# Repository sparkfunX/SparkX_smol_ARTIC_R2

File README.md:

# SparkX smôl ARTIC R2

[*SparkX smôl ARTIC R2 (SPX-18618)*](https://www.sparkfun.com/products/18618)

The ARGOS ARTIC R2 satellite communication chipset in smôl format.

## Repository Contents

- [**/Hardware**](./Hardware) - Eagle PCB, SCH and LBR design files
- [**LICENSE.md**](./LICENSE.md) - contains the licence information

## Product Versions

- [SPX-18618](https://www.sparkfun.com/products/18618) - Original SparkX Release.

## Thanks

The ARTIC R2 circuit is a remix of the reference design kindly provided by the [Arribada Initiative](https://arribada.org/) and Icoteq Ltd.

## License Information

This product is _**open source**_!

Please review the LICENSE.md file for license information.

If you have any questions or concerns on licensing, please contact technical support on our [SparkFun forums](https://forum.sparkfun.com/viewforum.php?f=123).

Distributed as-is; no warranty is given.

- Your friends at SparkFun.

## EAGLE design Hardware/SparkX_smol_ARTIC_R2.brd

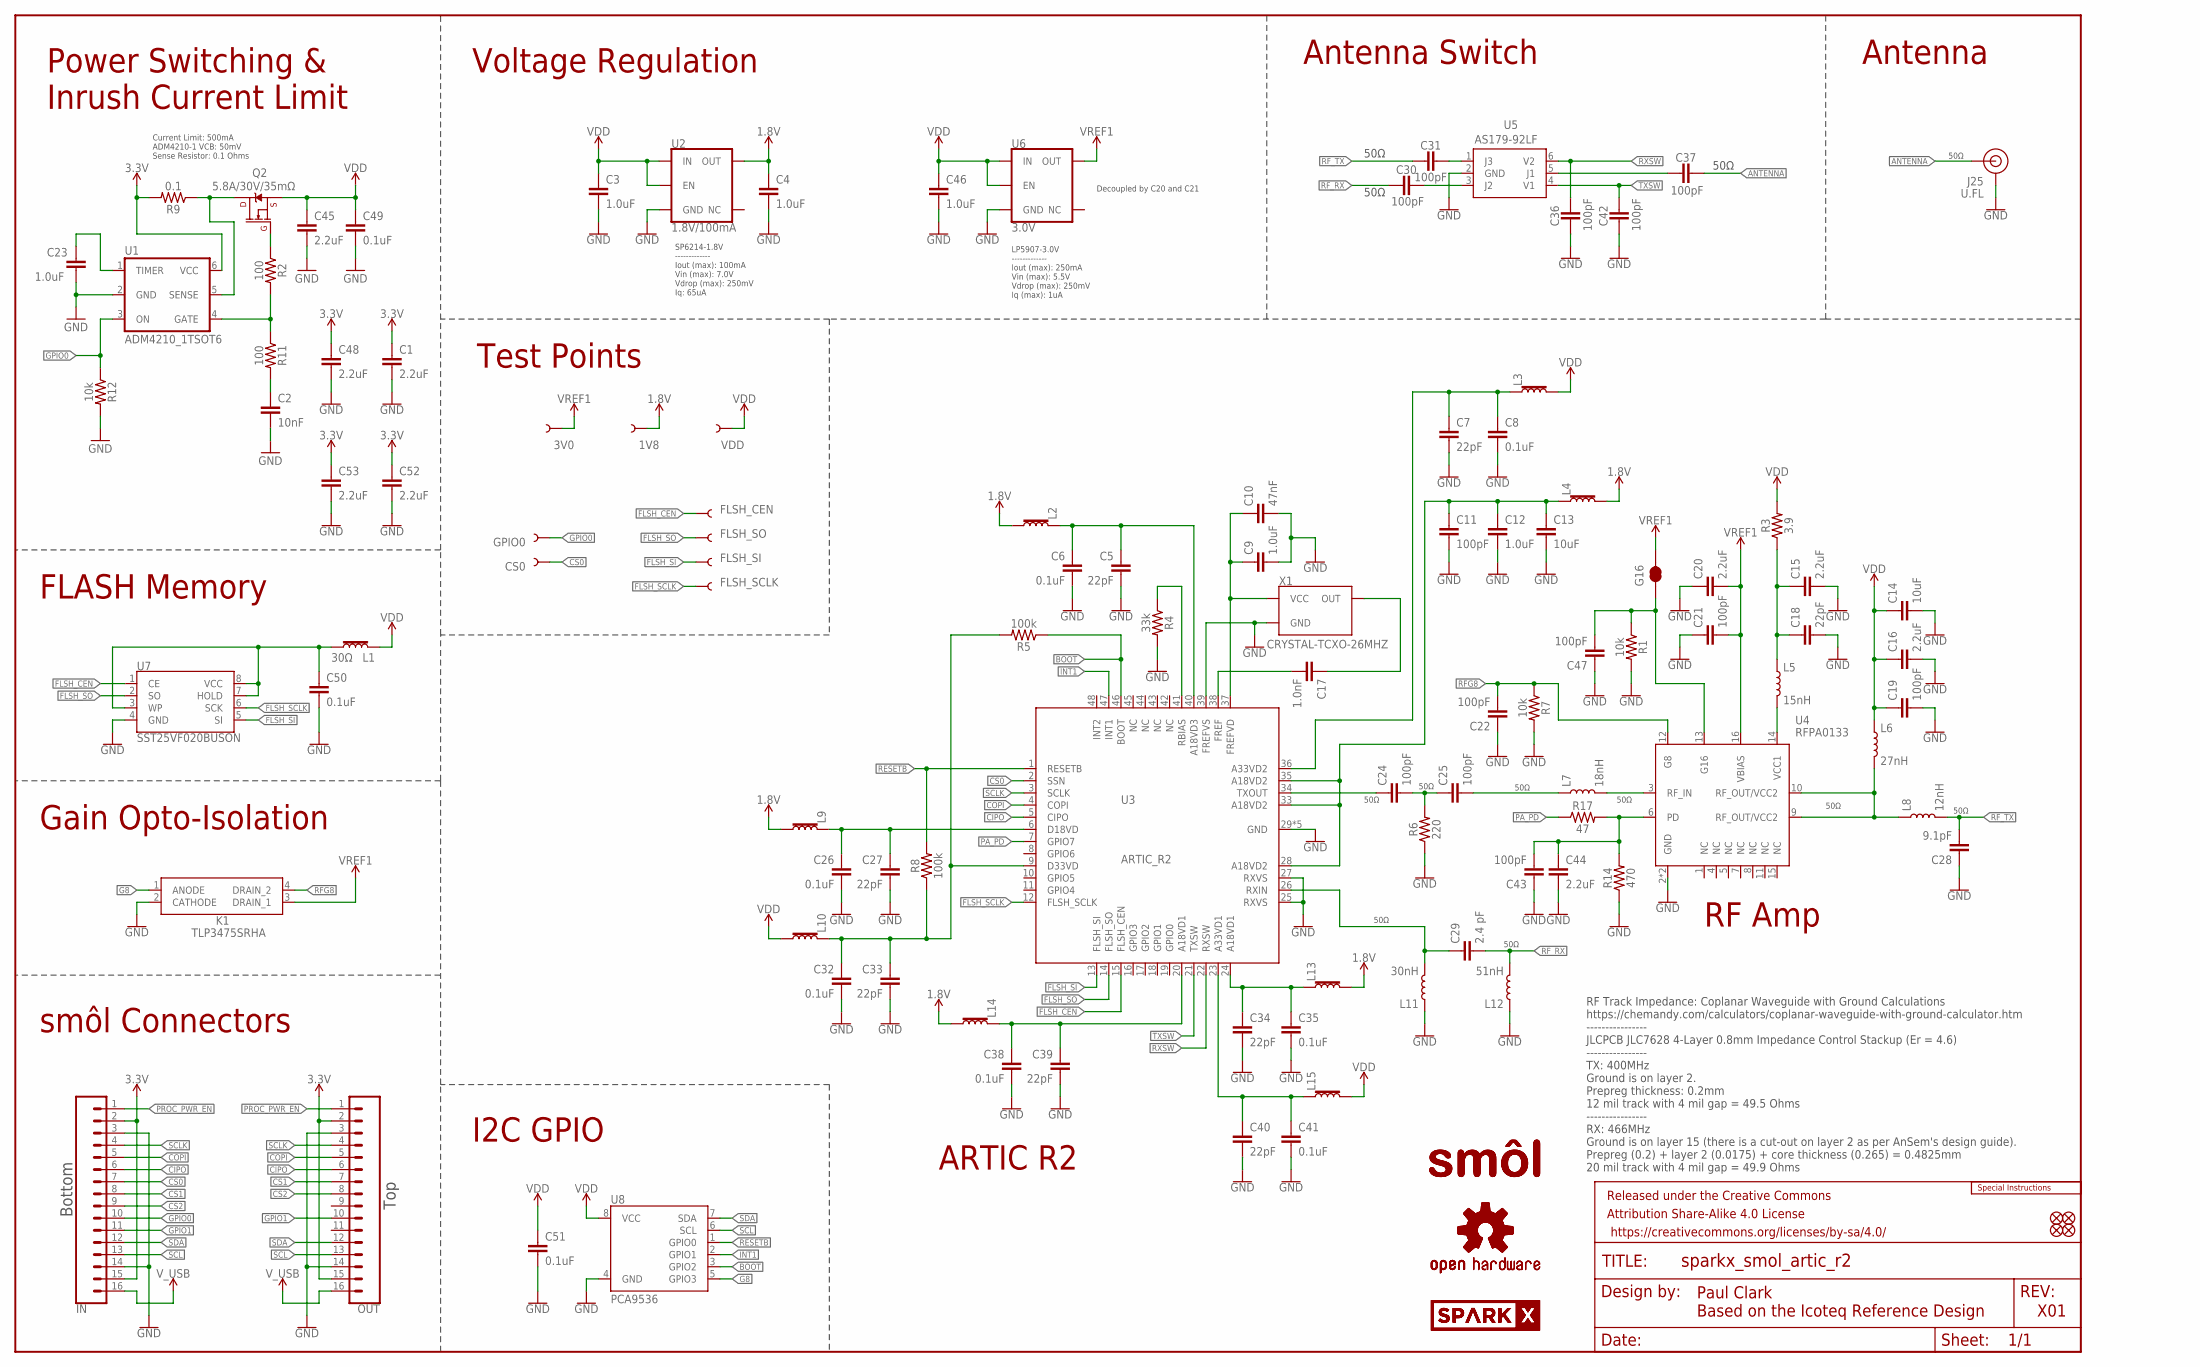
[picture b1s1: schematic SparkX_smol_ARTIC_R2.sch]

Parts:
1V8, 3V0: TEST-POINT3; PAD.03X.03
C1, C15, C16, C20, C44, C45, C48, C52, C53: 2.2uF; 0402-TIGHT
C2: 10nF; 0402-TIGHT
C3, C4, C9, C12, C23, C46: 1.0uF; 0402-TIGHT
C5, C7, C18, C27, C33, C34, C39, C40: 22pF; 0402-TIGHT
C6, C8, C26, C32, C35, C38, C41, C49, C50, C51: 0.1uF; 0402-TIGHT
C10: 47nF; 0402-TIGHT
C11, C19, C21, C22, C24, C25, C30, C31, C36, C37, C42, C43, C47: 100pF; 0402-TIGHT
C13, C14: 10uF; 0402-TIGHT
C17: 1.0nF; 0402-TIGHT
C28: 9.1pF; 0402-TIGHT
C29: 2.4 pF; 0402_MURATA
CS0: TEST-POINT3; PAD.03X.03
FD1, FD2, FD3, FD4: FIDUCIALUFIDUCIAL; FIDUCIAL-MICRO
FLSH_CEN: TEST-POINT3; PAD.03X.03
FLSH_SCLK: TEST-POINT3; PAD.03X.03
FLSH_SI: TEST-POINT3; PAD.03X.03
FLSH_SO: TEST-POINT3; PAD.03X.03
FRAME1: FRAME-LEDGER; CREATIVE_COMMONS
G16: JUMPER-SMT_2_NC_TRACE_NO-SILK; SMT-JUMPER_2_NC_TRACE_NO-SILK
GPIO0: TEST-POINT3; PAD.03X.03
IN: CONN_16FPC_16_0.5MM; FPC_16_0.5MM
J25: U.FL; U.FL_REDUCED_FOOTPRINT
K1: TLP3475SRHA
L1, L2, L3, L4, L9, L10, L13, L14, L15: 30Ω; 0402-TIGHT
L5: 15nH; 0402_COILCRAFT
L6: 27nH; 0402_COILCRAFT
L7: 18nH; 0402_COILCRAFT
L8: 12nH; 0402_COILCRAFT
L11: 30nH; 0402_COILCRAFT
L12: 51nH; 0402_COILCRAFT
LOGO1: SPECIAL_INSTRUCTIONS-ORDERING; ORDERING_INSTRUCTIONS
LOGO2, LOGO3: OSHW-LOGOMINI; OSHW-LOGO-MINI
OUT: CONN_16FPC_16_0.5MM; FPC_16_0.5MM
Q2: 5.8A/30V/35mΩ; SOT23-3
R1, R7, R12: 10k; 0402-TIGHT
R2, R11: 100; 0402-TIGHT
R3: 3.9; 0402-TIGHT
R4: 33k; 0402-TIGHT
R5, R8: 100k; 0402-TIGHT
R6: 220; 0402-TIGHT
R9: 0.1; 0603
R14: 470; 0402-TIGHT
R17: 47; 0402-TIGHT
U1: ADM4210_1TSOT6; TSOT6
U2: 1.8V/100mA; SC70
U3: ARTIC_R2; QFN-48
U4: RFPA0133; QFN50P300X300X86-17N
U5: AS179-92LF; SOT65P220X100-6N
U6: 3.0V; SOT23-5
U7: SST25VF020BUSON; USON_3X2MM
U8: PCA9536; MSOP8
U$2, U$3: SMOL_LOGOSMALL; SMOL_SMALL
U$4: SPARKX-LOGO3; SPARKX-SMALL
U$8: SPARKX-LOGO2; SPARKX-TINY
VDD: TEST-POINT3; PAD.03X.03
X1: CRYSTAL-TCXO-26MHZ; CRYSTAL-TCXO-SMD-1.65X1.25

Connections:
1.8V: 1V8.1, C4.1, L2.2, L4.2, L9.2, L13.2, L14.2, U2.5 (OUT)
3.3V: C1.1, C48.1, C52.1, C53.1, IN.2, IN.15, OUT.2, OUT.15, R9.2, U1.6 (VCC)
ANTENNA: C37.1, J25.FEED (SIGNAL)
BOOT: R5.1, U3.46 (BOOT), U8.3 (GPIO2)
CIPO: IN.6, OUT.6, U3.5 (CIPO)
COPI: IN.5, OUT.5, U3.4 (COPI)
CS0: CS0.1, IN.7, U3.2 (SSN)
CS1: IN.8, OUT.7
CS2: IN.9, OUT.8
FLASH_VCC: C50.1, L1.1, U7.3 (WP), U7.7 (HOLD), U7.8 (VCC)
FLSH_CEN: FLSH_CEN.1, U3.15 (FLSH_CEN), U7.1 (CE)
FLSH_SCLK: FLSH_SCLK.1, U3.12 (FLSH_SCLK), U7.6 (SCK)
FLSH_SI: FLSH_SI.1, U3.13 (FLSH_SI), U7.5 (SI)
FLSH_SO: FLSH_SO.1, U3.14 (FLSH_SO), U7.2 (SO)
G8: K1.1 (ANODE), U8.5 (GPIO3)
GND: C1.2, C2.2, C3.2, C4.2, C5.2, C6.2, C7.2, C8.2, C9.2, C10.2, C11.2, C12.2, C13.2, C14.2, C15.2, C16.2, C18.2, C19.2, C20.1, C21.1, C22.1, C23.2, C26.2, C27.2, C28.1, C32.2, C33.2, C34.2, C35.2, C36.2, C38.2, C39.2, C40.2, C41.2, C42.2, C43.1, C44.2, C45.2, C46.2, C47.1, C48.2, C49.2, C50.2, C51.2, C52.2, C53.2, IN.3, IN.14, J25.1 (GND), J25.2 (GND), K1.2 (CATHODE), L11.P$1 (1), L12.P$1 (1), OUT.3, OUT.14, R1.2, R4.2, R6.1, R7.2, R12.2, R14.1, U1.2 (GND), U2.2 (GND), U3.25 (RXVS), U3.27 (RXVS), U3.29 (GND), U3.30 (GND), U3.31 (GND), U3.32 (GND), U3.39 (FREFVS), U3.GND, U4.2 (GND), U4.EDAP (GND), U5.2 (GND), U6.2 (GND), U7.4 (GND), U8.4 (GND), X1.1 (GND), X1.2 (GND)
GPIO0: GPIO0.1, IN.10, R12.1, U1.3 (ON)
GPIO1: IN.11, OUT.10
INT1: U3.47 (INT1), U8.2 (GPIO1)
unnamed: Q2.3 (D), R9.1, U1.5 (SENSE)
unnamed: Q2.1 (G), R2.1
unnamed: R2.2, R11.1, U1.4 (GATE)
unnamed: C34.1, C35.1, L13.1, U3.24 (A18VD1)
unnamed: C40.1, C41.1, L15.1, U3.23 (A33VD1)
unnamed: C2.1, R11.2
unnamed: C23.1, U1.1 (TIMER)
unnamed: C26.1, C27.1, L9.1, U3.6 (D18VD)
unnamed: C32.1, C33.1, L10.1, R5.2, R8.1, U3.9 (D33VD)
unnamed: C11.1, C12.1, C13.1, L4.1, U3.28 (A18VD2), U3.33 (A18VD2), U3.35 (A18VD2)
unnamed: C7.1, C8.1, L3.1, U3.36 (A33VD2)
unnamed: R4.1, U3.41 (RBIAS)
unnamed: C5.1, C6.1, L2.1, U3.40 (A18VD3)
unnamed: C9.1, C10.1, U3.37 (FREFVD), X1.4 (VCC)
unnamed: C17.1, X1.3 (OUT)
unnamed: C17.2, U3.38 (FREF)
unnamed: C24.1, U3.34 (TXOUT)
unnamed: C24.2, C25.1, R6.2
unnamed: L5.P$2 (2), U4.14 (VCC1)
unnamed: C15.1, C18.1, L5.P$1 (1), R3.1
unnamed: C29.P$1 (1), L11.P$2 (2), U3.26 (RXIN)
unnamed: C25.2, L7.P$1 (1)
unnamed: L7.P$2 (2), U4.3 (RF_IN)
unnamed: L6.P$2 (2), L8.P$1 (1), U4.9 (RF_OUT/VCC2), U4.10 (RF_OUT/VCC2)
unnamed: C31.1, U5.1 (J3)
unnamed: C30.1, U5.3 (J2)
unnamed: C37.2, U5.5 (J1)
unnamed: C38.1, C39.1, L14.1, U3.20 (A18VD1)
PA_PD: R17.1, U3.7 (GPIO7)
PD: C43.2, C44.1, R14.2, R17.2, U4.6 (PD)
PROC_PWR_EN: IN.1, OUT.1
RESETB: R8.2, U3.1 (RESETB), U8.1 (GPIO0)
RFG8: C22.2, K1.4 (DRAIN_2), R7.1, U4.12 (G8)
RFG16: C47.2, G16.1, R1.1, U4.13 (G16)
RF_RX: C29.P$2 (2), C30.2, L12.P$2 (2)
RF_TX: C28.2, C31.2, L8.P$2 (2)
RXSW: C36.1, U3.22 (RXSW), U5.6 (V2)
SCL: IN.13, OUT.13, U8.6 (SCL)
SCLK: IN.4, OUT.4, U3.3 (SCLK)
SDA: IN.12, OUT.12, U8.7 (SDA)
TXSW: C42.1, U3.21 (TXSW), U5.4 (V1)
VDD: C3.1, C14.1, C16.1, C19.1, C45.1, C46.1, C49.1, C51.1, L1.2, L3.2, L6.P$1 (1), L10.2, L15.2, Q2.2 (S), R3.2, U2.1 (IN), U2.3 (EN), U6.1 (IN), U6.3 (EN), U8.8 (VCC), VDD.1
VREF1: 3V0.1, C20.2, C21.2, G16.2, K1.3 (DRAIN_1), U4.16 (VBIAS), U6.5 (OUT)
V_USB: IN.16, OUT.16

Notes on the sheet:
Paul Clark Based on the Icoteq Reference Design
X01
SP6214-1.8V ------------- Iout (max): 100mA Vin (max): 7.0V Vdrop (max): 250mV Iq: 65uA
Voltage Regulation
Antenna Switch
Antenna
ARTIC R2
RF Amp
Test Points
50Ω
RF Track Impedance: Coplanar Waveguide with Ground Calculations https://chemandy.com/calculators/coplanar-waveguide-with-ground-calculator.htm ---------------- JLCPCB JLC7628 4-Layer 0.8mm Impedance Control Stackup (Er = 4.6) ---------------- TX: 400MHz Ground is on layer 2. Prepreg thickness: 0.2m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
Gain Opto-Isolation
LP5907-3.0V ------------- Iout (max): 250mA Vin (max): 5.5V Vdrop (max): 250mV Iq (max): 1uA
Decoupled by C20 and C21
Power Switching & Inrush Current Limit
Current Limit: 500mA ADM4210-1 VCB: 50mV Sense Resistor: 0.1 Ohms
FLASH Memory
smôl Connectors
Bottom
Top
I2C GPIO

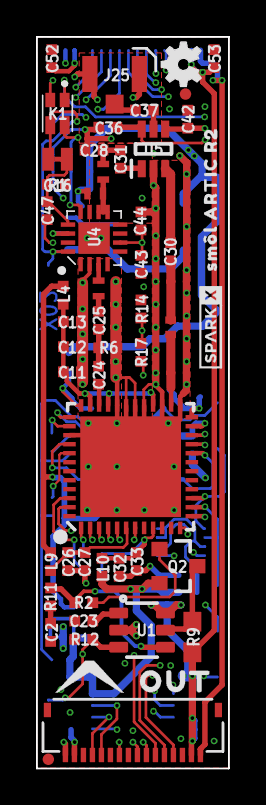
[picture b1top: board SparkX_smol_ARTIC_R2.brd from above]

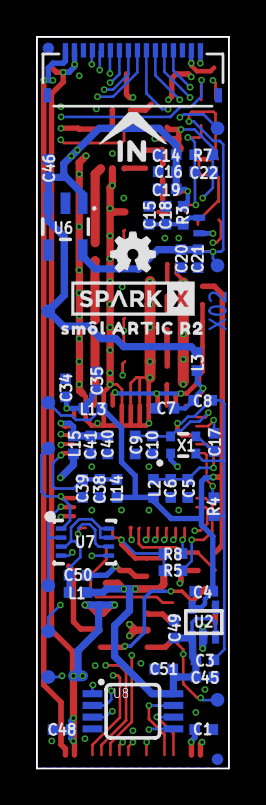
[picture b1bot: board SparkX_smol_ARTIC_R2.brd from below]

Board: 4 copper layers, 10.7 x 40.6 mm, 121 parts (64 on the bottom side), 63 nets.

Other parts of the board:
U$1: OUT0
U$7: IN0
U$9, U$10: SM�L_ARTIC_R20

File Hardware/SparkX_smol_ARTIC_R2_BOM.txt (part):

Partlist exported from C:/Users/pc235/Documents/EAGLE/SparkX_smol_ARTIC_R2/X02/SparkX_smol_ARTIC_R2.sch at 07/09/2021 13:14

Part      Value                         Device                          Package                       Description                                                                                                     DESCRIPTION                                               DESIGNER DIGIKEY_PART                             MANUFACTURER_NAME MANUFACTURER_PART_NUMBER MANU_PART                MOUSER_PART          MOUSER_PART_NUMBER PACKAGE   PROD_ID     REV VALUE        
1V8       TEST-POINT3                   TEST-POINT3                     PAD.03X.03                    SparkFun Test Points                                                                                                                                                                                                                                                                                                                                                           
3V0       TEST-POINT3                   TEST-POINT3                     PAD.03X.03                    SparkFun Test Points                                                                                                                                                                                                                                                                                                                                                           
C1        2.2uF                         2.2UF-0402_TIGHT-10V-10%-X5R    0402-TIGHT                    2.2µF ceramic capacitors                                                                                                                                                                                                                                                                                                                          CAP-14232       2.2uF        
C2        10nF                          10NF-0402T-25V-10%              0402-TIGHT                    0.01uF/10nF/10,000pF ceramic capacitors                                                                                                                                                                                                                                                                                                           CAP-14847       10nF         
C3        1.0uF                         1.0UF-0402T-16V-10%             0402-TIGHT                    1µF ceramic capacitors                                                                                                                                                                                                                                                                                                                            CAP-12417       1.0uF        
C4        1.0uF                         1.0UF-0402T-16V-10%             0402-TIGHT                    1µF ceramic capacitors                                                                                                                                                                                                                                                                                                                            CAP-12417       1.0uF        
C5        22pF                          22PF-0402T-16V-10%              0402-TIGHT                    22pF ceramic capacitors                                                                                                                                                                                                                                                                                                                           CAP-14674       22pF         
C6        0.1uF                         0.1UF-0402T-6.3V-10%-X7R        0402-TIGHT                    0.1µF ceramic capacitors                                                                                                                                                                                                                                                                                                                          CAP-14993       0.1uF        
C7        22pF                          22PF-0402T-16V-10%              0402-TIGHT                    22pF ceramic capacitors                                                                                                                                                                                                                                                                                                                           CAP-14674       22pF         
C8        0.1uF                         0.1UF-0402T-6.3V-10%-X7R        0402-TIGHT                    0.1µF ceramic capacitors                                                                                                                                                                                                                                                                                                                          CAP-14993       0.1uF        
C9        1.0uF                         1.0UF-0402T-16V-10%             0402-TIGHT                    1µF ceramic capacitors                                                                                                                                                                                                                                                                                                                            CAP-12417       1.0uF        
C10       47nF                          47NF-0402_TIGHT-25V-10%-X7R     0402-TIGHT                    47nF ceramic capacitors                                                                                                                                                                                                                                                                                                                           CAP-14243       47nF         
C11       100pF                         100PF-0402T-50V-5%              0402-TIGHT                    100pF/0.1nF ceramic capacitors                                                                                                                                                                                                                                                                                                                    CAP-13458       100pF        
C12       1.0uF                         1.0UF-0402T-16V-10%             0402-TIGHT                    1µF ceramic capacitors                                                                                                                                                                                                                                                                                                                            CAP-12417       1.0uF        
C13       10uF                          10UF-0402T-6.3V-20%             0402-TIGHT                    10.0µF ceramic capacitors                                                                                                                                                                                                                                                                                                                         CAP-14848       10uF         
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
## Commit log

2021-05-01 Routed
2021-05-02 Ready for review
2021-05-04 Review updates. Adding production files
2021-05-27 Gapless production panel
2021-06-09 Update 16-way FPC Connector
2021-07-30 Add Example1 - work in progress
2021-08-01 Add Example2
2021-08-02 Add Example3
2021-08-11 Fix glitch trapping in Example1. Improve power consumption in Example2.
2021-08-19 X02 - Add smôl branding
2021-08-20 Change EZ to smôl on schematic
2021-08-30 Add a link to the smôl examples in the ARTIC R2 library
2021-09-07 Add the BOM
2021-09-24 Change ADM4210-1 from IC-16020 to IC-14694
2021-10-28 Add product image
2021-10-28 Remove hookup guide content
    Hookup Guide: https://learn.sparkfun.com/tutorials/sml-artic-r2-hookup-guide

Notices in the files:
parts and their libraries:
SparkFun-Aesthetics: Licensing: Creative Commons ShareAlike 4.0 International - https://creativecommons.org/licenses/by-sa/4.0
SparkFun-Aesthetics: Released under the Creative Commons Attribution Share-Alike 4.0 License
SparkFun-Aesthetics: https://creativecommons.org/licenses/by-sa/4.0
